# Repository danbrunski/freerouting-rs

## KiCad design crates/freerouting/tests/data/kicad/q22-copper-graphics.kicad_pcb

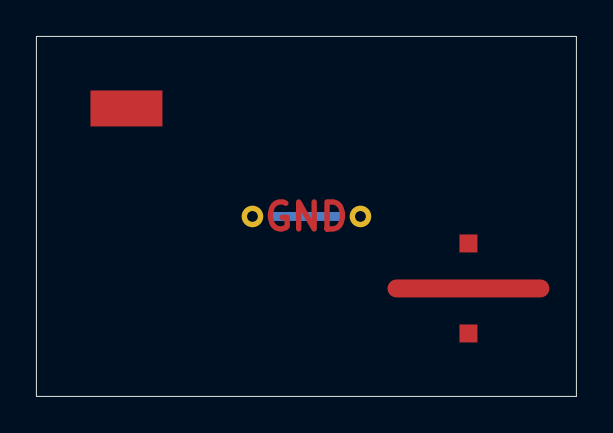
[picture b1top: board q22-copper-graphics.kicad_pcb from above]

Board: 2 copper layers, 30.0 x 20.0 mm, 4 parts (0 on the bottom side), 2 nets, no tracks yet.

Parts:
J1: x; jumper
J2: x; smdjumper
P1, P2: x; pad

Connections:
FG: P1.1, P2.1
N3: J2.1, J2.2

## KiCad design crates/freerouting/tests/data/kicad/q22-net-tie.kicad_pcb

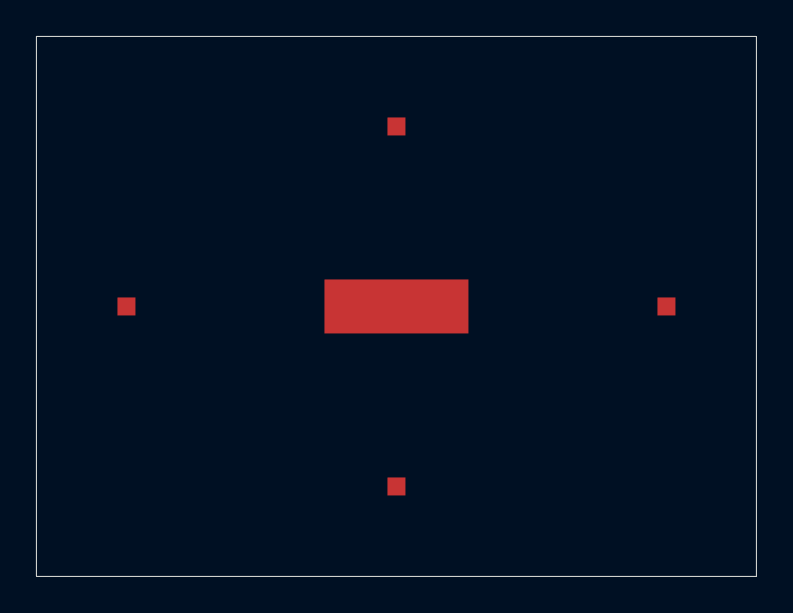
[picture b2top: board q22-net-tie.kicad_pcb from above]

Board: 2 copper layers, 40.0 x 30.0 mm, 5 parts (0 on the bottom side), 3 nets, no tracks yet.

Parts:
NT1: x; tie
PA: x; pad
PB: x; pad
PC1, PC2: x; pad

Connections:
A: NT1.1, PA.1
B: NT1.2, PB.1
C: PC1.1, PC2.1

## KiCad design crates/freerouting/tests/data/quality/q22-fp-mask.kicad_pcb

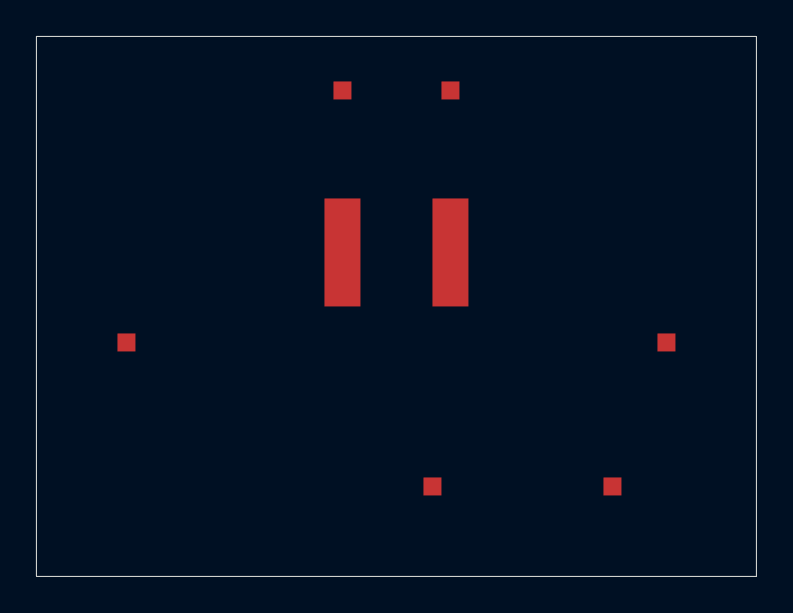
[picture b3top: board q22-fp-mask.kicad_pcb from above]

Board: 2 copper layers, 40.0 x 30.0 mm, 7 parts (0 on the bottom side), 4 nets, no tracks yet.

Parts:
J1: x; edge2
PA: x; pad
PB: x; pad
PC1, PC2: x; pad
PD: x; pad
U1: x; land

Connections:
A: J1.1, PA.1
B: J1.2, PB.1
C: PC1.1, PC2.1
D: PD.1, U1.1
